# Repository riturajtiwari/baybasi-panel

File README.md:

# Baybasi pixel wall

Software and firmware for a WS2812B video wall. The wall is 64 pixels wide and
192 pixels high. Each wall has 48 panels of 16 x 16 pixels.

There are two identical displays. The two displays do not share a cable, a
ground or a clock. Each display is a complete and independent system.

The software runs today without hardware. A software DDP sink receives the
pixel data and shows the result in a browser. You can test the driver and the
upload utility before the boards arrive.

---

## 1. The system

Each display contains these parts:

| Part | Quantity |
|---|---|
| Raspberry Pi 3 or newer, Pi OS Lite, headless | 1 |
| 8-port unmanaged switch | 1 |
| Controller board, one for each panel column | 4 |
| 16 x 16 WS2812B panel | 48 |

Each controller board holds an ESP32-S3-DevKitC-1, a WIZnet W5500 Ethernet
module and two SN74AHCT245N level shifters. Each board has 12 data outputs.
Each output drives one panel. The panels are not in a daisy chain. Thus one
strand has 256 LEDs and one frame needs 7.98 ms.

The Raspberry Pi holds all the geometry. A controller knows only the quantity
of bytes that it owns. All four controllers use the same firmware.

---

## 2. The contents of this repository

| Directory | Contents |
|---|---|
| `sw/` | The driver, the upload utility and the software DDP sink. Python. |
| `fw/` | The controller firmware. C++, PlatformIO, arduino-esp32 3.x. |
| `hw/` | The board design, the fabrication files and the enclosure. KiCad. |
| `HANDOFF-software.md` | The specification. |

`sw/README.md` and `fw/README.md` give more data about each part.

---

## 3. Before you start

You must have these programs:

- Python 3.9 or newer
- `ffmpeg` and `ffprobe`, on the PATH
- PlatformIO, but only to build the firmware

Install the software:

```bash
cd sw && python3 -m venv .venv && .venv/bin/pip install -e .
```

Make sure that the configuration is correct:

```bash
.venv/bin/baybasi check
```

The command shows the geometry and the wire budget. The command shows
`no problems found` if the configuration is correct.

---

## 4. Procedure: test the software without hardware

Do this procedure before the boards arrive. The procedure finds mapping errors
on a screen. You do not have to look at 8 feet of LEDs.

1. Start the software DDP sink in the first terminal:

   ```bash
   cd sw && .venv/bin/baybasi sink
   ```

2. Open `http://localhost:8088` in a browser.

3. Send a test pattern from the second terminal:

   ```bash
   cd sw && .venv/bin/baybasi pattern id --target 127.0.0.1
   ```

4. Look at the browser. Each of the 48 panels shows its own column number in
   yellow and its own row number in white. If a number is in the wrong
   position, correct the `panels:` list in `sw/config/wall.yaml`.

5. Send the other patterns. Refer to section 7.

6. Stop the pattern. Then start the driver and the upload utility:

   ```bash
   cd sw && .venv/bin/baybasi driver --target 127.0.0.1
   ```

   ```bash
   cd sw && .venv/bin/baybasi web
   ```

7. Open `http://localhost:8080`. Add a media file. Set the fit policy. Look at
   the preview.

**Caution: Do not send two patterns at the same time.** Two senders on UDP port
4048 cause torn frames. The sink shows a warning if this condition occurs.

---

## 5. Procedure: install on the Raspberry Pi

Do this procedure on each of the two Raspberry Pi computers.

```bash
sudo IFACE=eth0 PI_IP=192.168.50.1 ./sw/deploy/install.sh
```

The script does these tasks:

1. Installs Python, `ffmpeg` and `chrony`.
2. Installs the software in `/opt/baybasi`.
3. Puts the media library in `/var/lib/baybasi`.
4. Sets the wired interface to `192.168.50.1/24`.
5. Sets `ipv4.never-default yes` on that interface.
6. Starts the driver and the upload utility as services.

**The LED network must not become the default route.** The LED network has no
connection to the internet. If the LED network becomes the default route, the
Raspberry Pi loses DNS and NTP. NTP keeps the two displays in step.

---

## 6. Procedure: flash and commission a board

**Warning: Flash each board on the bench. Do not flash a board that is in a
controller.** A devkit in a controller with USB power sends 5 V out through the
power terminal. The 5 V can energize the panel column.

**Note:** Many USB-A to USB-C cables supply power only. Such a cable makes the
devkit port look defective. If the devkit does not show on the USB bus, replace
the cable first.

1. Connect the devkit to the computer with a USB-C data cable.

2. Build and flash the firmware:

   ```bash
   cd fw && pio run -t upload
   ```

3. Flash all 10 devkits at the same session. Then install the devkits in the
   controllers.

4. Connect the controller to the switch. Apply power.

5. Find the board on the Raspberry Pi:

   ```bash
   baybasi discover
   ```

   The board shows its factory MAC address. The column is empty.

6. Give the board its column:

   ```bash
   baybasi assign aa:bb:cc:dd:ee:ff 2
   ```

   The board writes the column to NVS. Then the board restarts. The board keeps
   the column after an update.

7. Do steps 4 to 6 for each of the four boards.

After the first flash, use the network for all subsequent updates:

```bash
baybasi ota .pio/build/baybasi-ctrl/firmware.bin --pi-ip 192.168.50.1
```

If an update fails, remove the devkit from its sockets. Then install a
different devkit.

---

## 7. The test patterns

```bash
baybasi pattern <name> --target 127.0.0.1
```

| Name | Function | What you must see |
|---|---|---|
| `id` | Panel identification | Each panel shows its column and its row. |
| `strand` | Output identification | Each output has a different colour. |
| `chase` | LED chain | A comet moves smoothly along the chain. |
| `scroll` | Frame synchronization | A white column moves across the wall. The line does not break at the column seams. |
| `bars` | Colour order | The top band is red. |
| `gray` | Gamma and dither | A smooth ramp. There are no bands. |
| `solid` | Power supply | A flat colour. |

`scroll` is the most important pattern. Only `scroll` shows a synchronization
error between the four controllers.

**Caution: `solid` at full white causes the maximum current.** Do not use
`solid` at full white before the power injection is correct.

---

## 8. Configuration

`sw/config/wall.yaml` holds all the geometry. The file is data and not code.
You can correct an error in the wall with a text editor. You do not have to
change the Python code.

The file contains these items:

| Item | Function |
|---|---|
| `panel.chain` | The sequence of the 256 LEDs in one panel. |
| `controllers[].panels` | The wall row that each output drives. |
| `transform` | The rotation of one panel. Use this for a panel that is upside down. |
| `color_order` | The channel sequence on the network. |
| `render` | The frame rate, the gamma, the brightness and the epoch. |
| `network` | The addresses, the port and the packet size. |

Example: row 7 of column 2 shows the picture of row 8. To correct this error,
change two lines in the `panels:` list. Then restart the driver.

---

## 9. The status LED

The status LED is the only indication that you can see when the board is behind
a panel.

| Colour | Condition |
|---|---|
| Red | The board is in the start sequence. |
| Red, slow flash | There is no Ethernet link. |
| Amber | The link is up. There are no pixels for more than 500 ms. |
| Blue | The board receives data. The outputs are off. |
| Green, slow pulse | The board operates correctly. |
| Magenta | The frames are not complete. |
| White, pulse | An update is in progress. |
| White, fast flash | The operator sent a Find command. |
| Red, fast flash | There is a fault. Read the serial log. |

---

## 10. Keep the two displays in step

No messages go between the two displays. Each Raspberry Pi calculates the frame
number from the time of day:

```python
frame_index = int((time.time() - EPOCH) * FPS) % n_frames
```

Thus the two displays agree only if the two playlists are the same. The
playlist compiles to a frame timeline. The manifest digest is a hash of that
timeline.

Procedure:

1. Upload the same media to the first Raspberry Pi.
2. Upload the same media to the second Raspberry Pi.
3. Download the manifest from the second Raspberry Pi.
4. Use the **Compare** button on the first Raspberry Pi.

If the two digests agree, the two walls show the same content. If the two
digests do not agree, the utility gives the reason:

```
$ baybasi manifest --compare pi-b.json
DIFFERS:
  sunset.jpg: fit letterbox vs crop
  same media, different playlist order
```

The `EPOCH` value in `wall.yaml` must be the same on the two computers. The
`wall_digest` value must also be the same.

---

## 11. Troubleshooting

| Symptom | Cause | Correction |
|---|---|---|
| The sink shows torn frames and a high gap count. | Two senders transmit on port 4048. | Stop the other `baybasi pattern` or `baybasi driver`. |
| The wall shows noise at power-up. | The level shifters became active too soon. | Measure GPIO 8. GPIO 8 must stay high until the first complete frame. Check R15 to the 3V3E rail. |
| The wall keeps one picture after a fault. | The controller still receives packets. | Look at the driver log. A controller goes to black 500 ms after the last packet. |
| Red and green are not correct. | The Pi and the firmware both change the channel order. | Set `LED_ORDER_GRB` to 0 in `fw/src/config.h`. Refer to section 12. |
| The driver reports dropped frames. | The Raspberry Pi cannot do the work in time. | Read the stage times in `baybasi status`. The slowest stage is the cause. |
| The board does not show in `baybasi discover`. | There is no link, or the board has no address. | Look at the status LED. A red flash shows that there is no link. |
| The two walls do not agree. | The playlists are different. | Compare the manifests. Refer to section 10. |

---

## 12. Two decisions that the specification did not make

**The network carries RGB. The firmware changes the sequence to GRB.** The
WS2812B is a GRB device, but that is a property of the LED and not of the
network. The DDP data-type byte declares RGB. Thus a GRB payload would give
incorrect data to Wireshark and to other DDP tools.

One flag controls each side: `color_order` in `wall.yaml`, and `LED_ORDER_GRB`
in `fw/src/config.h`. Only one of the two must change the sequence. The `bars`
pattern shows which condition is true. The top band must be red.

**Each controller has its own DDP destination identifier, 10 to 13.** The four
boards are still different only by IP address. The identifier comes from the
column number. The firmware also accepts identifier 1 and identifier 255. The
byte counts do not change.

The identifier gives two advantages. One software sink on one computer can
replace four boards on four addresses. A packet that goes to the incorrect
board is rejected and not shown.

---

## 13. Tests

Python, 70 tests:

```bash
cd sw && .venv/bin/python -m pytest tests -q
```

Firmware logic, 20 tests. The tests run on the host computer:

```bash
cd fw && clang++ -std=c++17 -O1 -g -fsanitize=thread -I test/shim \
    -o /tmp/fwtest test/test_framebuf.cpp src/framebuf.cpp && /tmp/fwtest
```

---

## 14. The condition of this project

The software is complete and tested. A measured run gives 30.0 frames each
second with 0 torn frames and 0 protocol errors. The Raspberry Pi work is
3.0 ms of the 33.3 ms budget.

The firmware is complete but **no person has flashed the firmware to a board**.
The boards are in fabrication. Only the frame assembler is proven. The frame
assembler compiles on the host computer and passes the thread tests.

These items are not proven:

- The Ethernet start sequence
- The `/OE` sequence at power-up
- The update through the network
- The LED library with the 12 pins of the board

Do these three checks first at the bench:

1. The serial log shows the factory MAC address and a successful `ETH.begin`.
2. `baybasi discover` finds the board.
3. `baybasi pattern bars` lights the panels. The top band is red. There is no
   flash at power-up.

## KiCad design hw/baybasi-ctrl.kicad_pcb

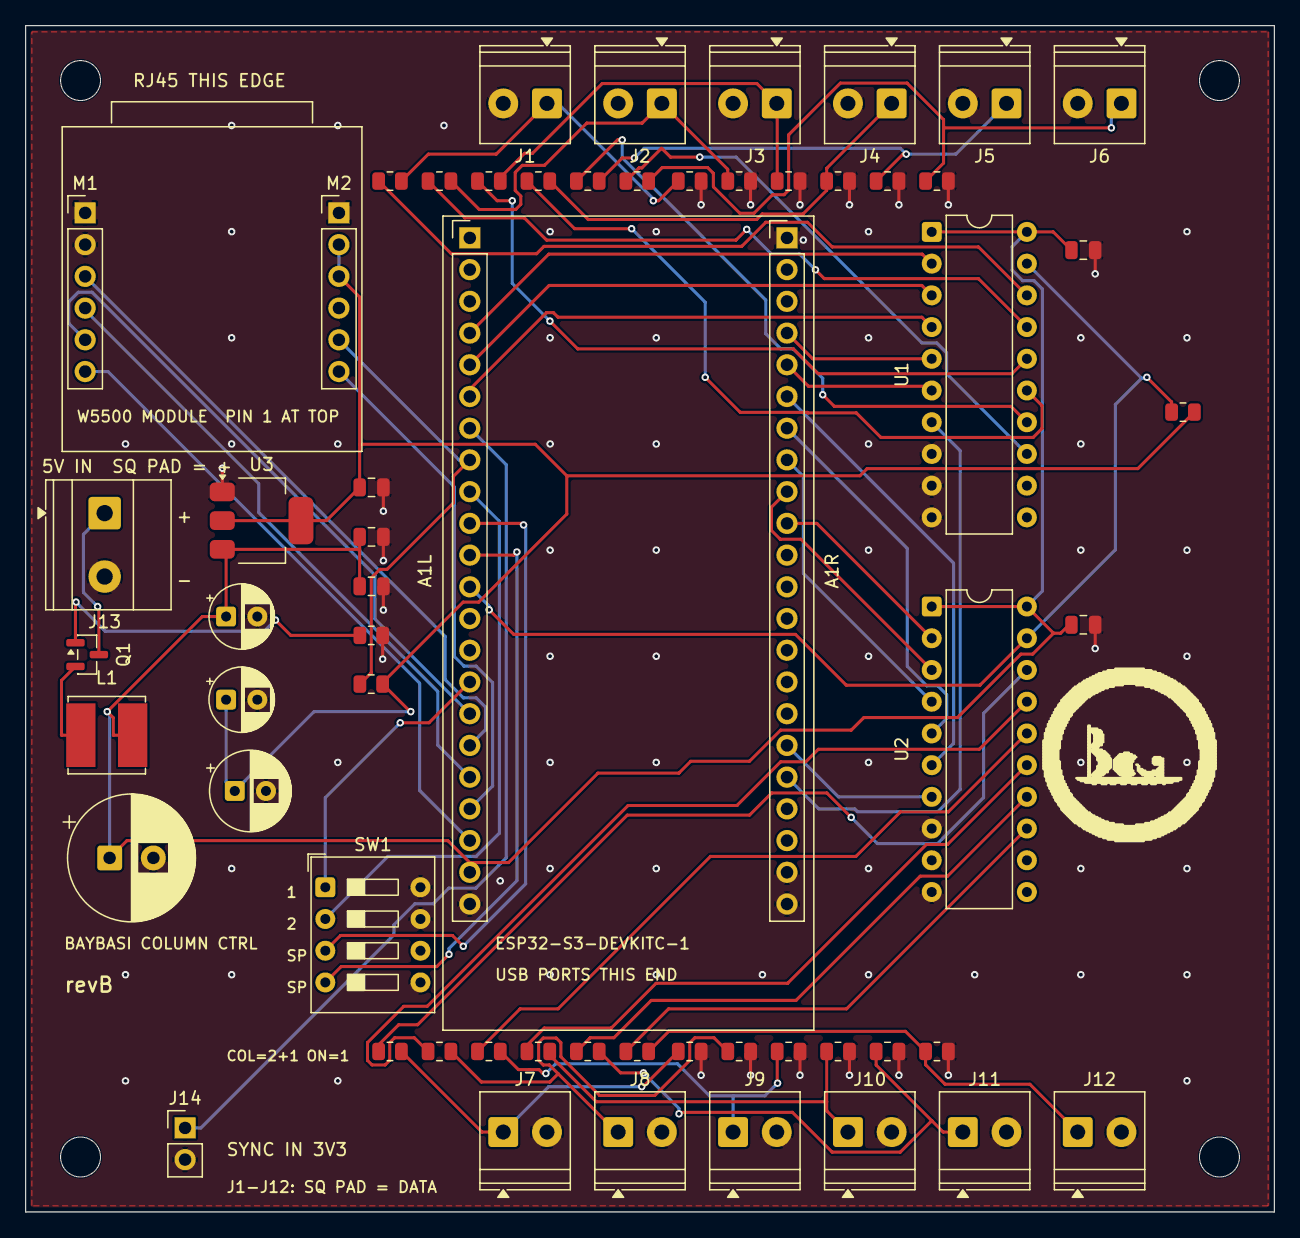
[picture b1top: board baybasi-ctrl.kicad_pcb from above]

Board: 2 copper layers, 100.0 x 95.0 mm, 64 parts (0 on the bottom side), 54 nets.

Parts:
A1L, A1R: PinHeader_1x22_P2.54mm_Vertical
C1: CP_Radial_D10.0mm_P3.50mm
C2: CP_Radial_D6.3mm_P2.50mm
C3, C4: CP_Radial_D5.0mm_P2.50mm
C5, C6, C7, C8, C9: C_0805_2012Metric
H1, H2, H3, H4: MountingHole_3.2mm_M3
J1, J2, J3, J4, J5, J6, J7, J8, J9, J10, J11, J12: TerminalBlock_Phoenix_PT-1,5-2-3.5-H_1x02_P3.50mm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; TerminalBlock_Phoenix_PT-1,5-2-3.5-H_1x02_P3.50mm_Horizontal
J13: TerminalBlock_Phoenix_MKDS-1,5-2-5.08_1x02_P5.08m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; TerminalBlock_Phoenix_MKDS-1,5-2-5.08_1x02_P5.08mm_Horizont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
J14: PinHeader_1x02_P2.54mm_Vertical
L1: L_Bourns_SRN6045TA
M1, M2: PinHeader_1x06_P2.54mm_Vertical
Q1: SOT-23
R1, R2, R3, R4, R5, R6, R7, R8, R9, R10, R11, R12, R13, R14, R15, R16, R17, R18, R19, R20, R21, R22, R23, R24, R25, R26, R27: R_0805_2012Metric
SW1: SW_DIP_SPSTx04_Slide_9.78x12.34mm_W7.62mm_P2.54mm
U1, U2: DIP-20_W7.62mm
U3: SOT-223-3_TabPin2

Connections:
+3V3E: C2.1, C4.1, C7.1, M2.2, M2.3, R14.2, R15.2, U3.2
+5V: A1L.21, C1.1, C3.1, C5.1, C6.1, C8.1, C9.1, L1.2, U1.1, U1.20, U2.1, U2.20, U3.3
COL_B0: A1L.15, SW1.1
COL_B1: A1L.9, SW1.2
COL_SP0: A1L.10, SW1.3
COL_SP1: A1L.11, SW1.4
D1_3V3: A1L.4, U1.2
D1_5V: R1.1, U1.18
D2_3V3: A1L.5, U1.3
D2_5V: R2.1, U1.17
D3_3V3: A1L.6, U1.4
D3_5V: R3.1, U1.16
D4_3V3: A1R.4, U1.5
D4_5V: R4.1, U1.15
D5_3V3: A1R.5, U1.6
D5_5V: R5.1, U1.14
D6_3V3: A1R.18, U1.7
D6_5V: R6.1, U1.13
D7_3V3: A1R.10, U2.2
D7_5V: R7.1, U2.18
D8_3V3: A1R.9, U2.3
D8_5V: R8.1, U2.17
D9_3V3: A1R.8, U2.4
D9_5V: R9.1, U2.16
D10_3V3: A1R.7, U2.5
D10_5V: R10.1, U2.15
D11_3V3: A1R.6, U2.6
D11_5V: R11.1, U2.14
D12_3V3: A1R.17, U2.7
D12_5V: R12.1, U2.13
ETH_CS: A1L.16, M1.5
ETH_INT: A1L.20, M1.6
ETH_MISO: A1L.19, M2.6
ETH_MOSI: A1L.17, M1.3
ETH_RST: A1L.8, M2.5, R14.1
ETH_SCK: A1L.18, M1.4
GND: A1L.22, A1R.1, A1R.21, A1R.22, C1.2, C2.2, C3.2, C4.2, C5.2, C6.2, C7.2, C8.2, C9.2, J1.2, J2.2, J3.2, J4.2, J5.2, J6.2, J7.2, J8.2, J9.2, J10.2, J11.2, J12.2, J13.2, J14.2, M1.1, M1.2, M2.1, R13.2, R16.2, R17.2, R18.2, R19.2, R20.2, R21.2, R22.2, R23.2, R24.2, R25.2, R26.2, R27.2, SW1.5, SW1.6, SW1.7, SW1.8, U1.8, U1.9, U1.10, U2.8, U2.9, U2.10, U3.1
OE_N: A1L.12, R15.1, U1.19, U2.19
OUT1: J1.1, R1.2, R16.1
OUT2: J2.1, R2.2, R17.1
OUT3: J3.1, R3.2, R18.1
OUT4: J4.1, R4.2, R19.1
OUT5: J5.1, R5.2, R20.1
OUT6: J6.1, R6.2, R21.1
OUT7: J7.1, R7.2, R22.1
OUT8: J8.1, R8.2, R23.1
OUT9: J9.1, R9.2, R24.1
OUT10: J10.1, R10.2, R25.1
OUT11: J11.1, R11.2, R26.1
OUT12: J12.1, R12.2, R27.1
SYNC_IN: A1L.7, J14.1
V5_PROT: L1.1, Q1.2
VGATE: Q1.1, R13.1
VIN_RAW: J13.1, Q1.3

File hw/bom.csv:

"Reference","Value","Footprint","QUANTITY"
"A1","ESP32-S3-DevKitC-1","PCM_Espressif:ESP32-S3-DevKitC","1"
"C1","470uF 16V","Capacitor_THT:CP_Radial_D10.0mm_P3.50mm","1"
"C2","100uF","Capacitor_THT:CP_Radial_D6.3mm_P2.50mm","1"
"C3","10uF","Capacitor_THT:CP_Radial_D5.0mm_P2.50mm","1"
"C4","22uF","Capacitor_THT:CP_Radial_D5.0mm_P2.50mm","1"
"C5-C9","100nF","Capacitor_SMD:C_0805_2012Metric","5"
"J1","PANEL 1","TerminalBlock_Phoenix:TerminalBlock_Phoenix_PT-1,5-2-3.5-H_1x02_P3.50mm_Horizontal","1"
"J2","PANEL 2","TerminalBlock_Phoenix:TerminalBlock_Phoenix_PT-1,5-2-3.5-H_1x02_P3.50mm_Horizontal","1"
"J3","PANEL 3","TerminalBlock_Phoenix:TerminalBlock_Phoenix_PT-1,5-2-3.5-H_1x02_P3.50mm_Horizontal","1"
"J4","PANEL 4","TerminalBlock_Phoenix:TerminalBlock_Phoenix_PT-1,5-2-3.5-H_1x02_P3.50mm_Horizontal","1"
"J5","PANEL 5","TerminalBlock_Phoenix:TerminalBlock_Phoenix_PT-1,5-2-3.5-H_1x02_P3.50mm_Horizontal","1"
"J6","PANEL 6","TerminalBlock_Phoenix:TerminalBlock_Phoenix_PT-1,5-2-3.5-H_1x02_P3.50mm_Horizontal","1"
"J7","PANEL 7","TerminalBlock_Phoenix:TerminalBlock_Phoenix_PT-1,5-2-3.5-H_1x02_P3.50mm_Horizontal","1"
"J8","PANEL 8","TerminalBlock_Phoenix:TerminalBlock_Phoenix_PT-1,5-2-3.5-H_1x02_P3.50mm_Horizontal","1"
"J9","PANEL 9","TerminalBlock_Phoenix:TerminalBlock_Phoenix_PT-1,5-2-3.5-H_1x02_P3.50mm_Horizontal","1"
"J10","PANEL 10","TerminalBlock_Phoenix:TerminalBlock_Phoenix_PT-1,5-2-3.5-H_1x02_P3.50mm_Horizontal","1"
"J11","PANEL 11","TerminalBlock_Phoenix:TerminalBlock_Phoenix_PT-1,5-2-3.5-H_1x02_P3.50mm_Horizontal","1"
"J12","PANEL 12","TerminalBlock_Phoenix:TerminalBlock_Phoenix_PT-1,5-2-3.5-H_1x02_P3.50mm_Horizontal","1"
"J13","5V IN","TerminalBlock_Phoenix:TerminalBlock_Phoenix_MKDS-1,5-2-5.08_1x02_P5.08mm_Horizontal","1"
"J14","SYNC IN (opt)","Connector_PinHeader_2.54mm:PinHeader_1x02_P2.54mm_Vertical","1"
"L1","10uH 2A","Inductor_SMD:L_Bourns_SRN6045TA","1"
"M1","WIZ850io J1","Connector_PinHeader_2.54mm:PinHeader_1x06_P2.54mm_Vertical","1"
"M2","WIZ850io J2","Connector_PinHeader_2.54mm:PinHeader_1x06_P2.54mm_Vertical","1"
"Q1","AO3401A","Package_TO_SOT_SMD:SOT-23","1"
"R1-R12","330","Resistor_SMD:R_0805_2012Metric","12"
"R13","100k","Resistor_SMD:R_0805_2012Metric","1"
"R14,R15","10k","Resistor_SMD:R_0805_2012Metric","2"
"U1,U2","SN74AHCT245N","Package_DIP:DIP-20_W7.62mm","2"
"U3","AMS1117-3.3","Package_TO_SOT_SMD:SOT-223-3_TabPin2","1"

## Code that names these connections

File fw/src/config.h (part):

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#define FW_VERSION FW_SEMVER "+" FW_GIT

// ---- W5500 on SPI ---------------------------------------------------------
static constexpr int PIN_ETH_CS   = 10;   // devkit pad 16, FSPI IOMUX
static constexpr int PIN_ETH_MOSI = 11;   // pad 17
static constexpr int PIN_ETH_SCK  = 12;   // pad 18
static constexpr int PIN_ETH_MISO = 13;   // pad 19
static constexpr int PIN_ETH_INT  = 14;   // pad 20
static constexpr int PIN_ETH_RST  = 15;   // pad 8, active low, 10k to 3V3E
// Overridable so the bench can drop it without editing this file:
//   PLATFORMIO_BUILD_FLAGS="-DETH_SPI_MHZ_CFG=4" pio run
// 25 MHz is well inside the W5500's 33 MHz ceiling, but it crosses two socket
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#else
#define COLUMN_DIP 0
#endif
static constexpr int     PIN_COL_B0   = 9;    // SW1 pole 1, silkscreen "1"
static constexpr int     PIN_COL_B1   = 16;   // SW1 pole 2, silkscreen "2"
static constexpr uint8_t COL_IP_BASE  = 11;   // column c -> 192.168.50.(11 + c)
static constexpr uint8_t COL_DDP_BASE = 10;   // column c -> DDP id (10 + c)

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
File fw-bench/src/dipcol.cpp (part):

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#endif

// Column select, rev B. Confirmed against hw/gen_sch.py: devkit pad 15 = GPIO 9
// = COL_B0, pad 9 = GPIO 16 = COL_B1, pad 10 = GPIO 17, pad 11 = GPIO 18.
// Every pole's common side is GND, so the internal pull-up makes an OPEN switch
// read 1 and a CLOSED switch read 0 - and the firmware inverts. Closed = 1.
#define PIN_COL_B0  9    // silkscreen "1", binary weight 1
#define PIN_COL_B1  16   // silkscreen "2", binary weight 2
#define PIN_COL_SP0 17   // silkscreen "SP", unread in production
#define PIN_COL_SP1 18   // silkscreen "SP", unread in production

#define PANEL_W 16
#define PANEL_H 16
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static Switches readSwitches() {
    // Closed pulls to GND, so an OPEN pin reads HIGH. Invert: closed = true = 1.
    Switches s;
    s.b0  = !digitalRead(PIN_COL_B0);
    s.b1  = !digitalRead(PIN_COL_B1);
    s.sp0 = !digitalRead(PIN_COL_SP0);
    s.sp1 = !digitalRead(PIN_COL_SP1);
    s.col = (uint8_t)((s.b1 ? 2 : 0) | (s.b0 ? 1 : 0));
    return s;
}
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        s.col, COL_NAME[s.col],
        s.b1 ? "ON " : "off", s.b0 ? "ON " : "off",
        s.sp0 ? "ON " : "off", s.sp1 ? "ON " : "off",
        digitalRead(PIN_COL_B1), digitalRead(PIN_COL_B0),
        digitalRead(PIN_COL_SP0), digitalRead(PIN_COL_SP1));
}

static void banner() {
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    Serial.println("=== Baybasi rev B bring-up: one panel + column DIP ===");
    Serial.printf("  panel out   D1  -> GPIO %d -> R1 -> U1 -> J1\n", LED_PIN);
    Serial.printf("  /OE         GPIO %d, LOW enables both 245s\n", OE_PIN);
    Serial.printf("  col bit 0   GPIO %d   silkscreen \"1\", weight 1\n", PIN_COL_B0);
    Serial.printf("  col bit 1   GPIO %d   silkscreen \"2\", weight 2\n", PIN_COL_B1);
    Serial.printf("  spares      GPIO %d, %d   silkscreen \"SP\"\n",
                  PIN_COL_SP0, PIN_COL_SP1);
    Serial.println("  switch CLOSED (ON, toward the GND pads) = 1");
    Serial.println();
    Serial.println("  [2] [1]  column        [2] [1]  column");
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    while (!Serial && millis() - t0 < 2000) delay(10);
    banner();

    pinMode(PIN_COL_B0,  INPUT_PULLUP);
    pinMode(PIN_COL_B1,  INPUT_PULLUP);
    pinMode(PIN_COL_SP0, INPUT_PULLUP);
    pinMode(PIN_COL_SP1, INPUT_PULLUP);
    delay(5);                       // let the internal pull-ups settle

    FastLED.addLeds<WS2812B, LED_PIN, GRB>(leds, PANEL_LEDS);
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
